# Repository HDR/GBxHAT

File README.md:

# GBxHAT

**A GBxCart RW in PiZero Hat format**

Purchase on [OSHPark](https://oshpark.com/shared_projects/nTx9yzmZ)

Uses the original schematic by [InsideGadgets](https://github.com/insidegadgets/GBxCart-RW) with some changes

Uses the Pi Zero HAT template by [Mike Lawrence](https://github.com/mikelawrence/RPi_Zero_pHat_Template)

The CH340 was removed, as TX and RX are connected straight to the pi zero

[Interactive BOM](https://martinrefseth.com/ibom/GBxHat)

**Keep in mind that this is untested and has no software**

## Images

## Notes

- Please cut pin 4 on the pi if your hat is not the revision published after July 18th 2020.

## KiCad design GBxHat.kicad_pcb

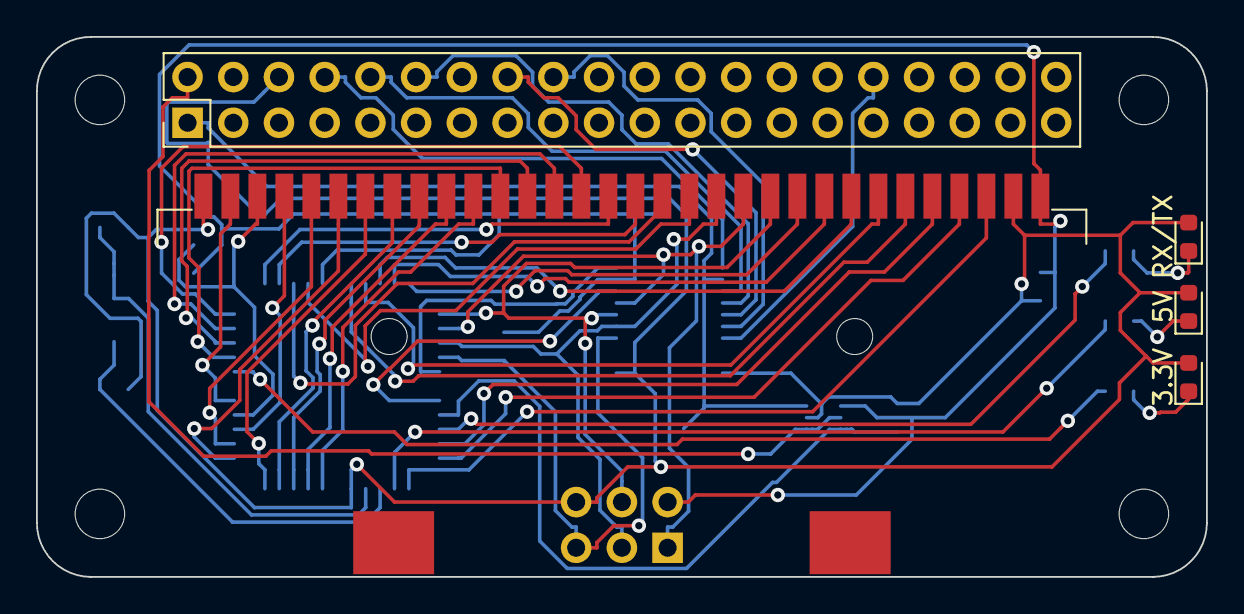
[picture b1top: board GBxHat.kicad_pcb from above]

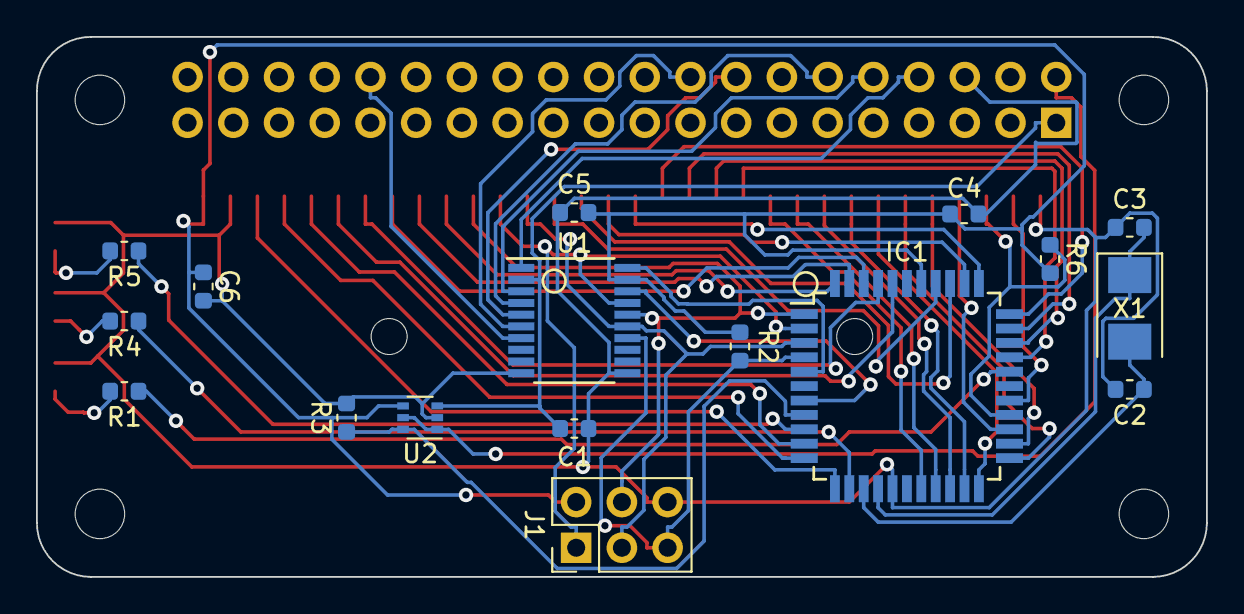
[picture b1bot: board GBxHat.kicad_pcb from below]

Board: 2 copper layers, 65.0 x 30.0 mm, 26 parts (17 on the bottom side), 51 nets.

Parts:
3.3V: 3.3V LED; LED_0603_1608Metric
5V: 5V LED; LED_0603_1608Metric
C1, C4, C5, C6: 0.1uF; C_0603_1608Metric
C2, C3: 18pF; C_0603_1608Metric
IC1: ATMEGA8515L-8AU; TQFP-44_10x10mm_P0.8mm
J0: Pi Zero; PinHeader_2x20_P2.54mm_Vertical
J1: AVR_SPI_6; PinHeader_2x03_P2.54mm_Vertical
MH1, MH2, MH3, MH4: MountingHole; RPi_Hat_Mounting_Hole
R1, R2, R3, R4, R5, R6: 10K; R_0603_1608Metric
RX/TX: RX/TX LED; LED_0603_1608Metric
U1: TXB0108PWR; TSSOP-20_4.4x6.5mm_P0.65mm
U2: NLAS4157; SOT-363_SC-70-6
U$1: GB_CARTWITH_HOLES; DSL_Cartridge_Reader
X1: 8MHz; Crystal_SMD_5032-2Pin_5.0x3.2mm

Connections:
3.3V: C1.1, J0.1, U1.2, U2.3
5V: J0.2, U2.1, U2.5
/*MREQ/CS: IC1.10, U$1.5
/*RD: IC1.11, U$1.4
/*RESET/CS2: IC1.26, R6.1, U$1.30
/*WR: IC1.12, U$1.3
/A0: IC1.40, U$1.6
/A1: IC1.41, U$1.7
/A2: IC1.42, U$1.8
/A3: IC1.43, U$1.9
/A4: IC1.44, U$1.10
/A5/MOSI: IC1.1, J1.4, U1.16, U$1.11
/A6/MISO: IC1.2, J1.1, U1.17, U$1.12
/A7/SCK: IC1.3, J1.3, U1.15, U$1.13
/A8: IC1.37, U$1.14
/A9: IC1.36, U$1.15
/A10: IC1.35, U$1.16
/A11: IC1.34, U$1.17
/A12: IC1.33, U$1.18
/A13: IC1.32, U$1.19
/A14: IC1.31, U$1.20
/A15: IC1.30, U$1.21
/ATMEGA_RX_OUT: IC1.5, U1.20
/ATMEGA_TX_OUT: IC1.7, U1.18
/AUDIO_IN: IC1.27, U$1.31
/D0: IC1.18, U$1.22
/D1: IC1.19, U$1.23
/D2: IC1.20, U$1.24
/D3: IC1.21, U$1.25
/D4: IC1.22, U$1.26
/D5: IC1.23, U$1.27
/D6: IC1.24, U$1.28
/D7: IC1.25, U$1.29
/PI_MISO: J0.12, U1.4
/PI_MOSI: J0.16, U1.5
/PI_RESET: J0.32, U1.7
/PI_RX_IN: J0.8, U1.1
/PI_SCK: J0.18, U1.6
/PI_TX_IN: J0.10, U1.3
/RESET: IC1.4, J1.5, R2.1, U1.14
/SPDT_SEL: IC1.8, R3.1, U2.6
GND: 3.3V.2, 5V.2, C1.2, C2.2, C3.2, C4.2, C5.2, C6.2, IC1.16, J0.6, J1.6, R3.2, RX/TX.2, U1.10, U1.11, U2.2, U$1.2, U$1.32
unnamed: C2.1, IC1.14, X1.2
unnamed: C3.1, IC1.15, X1.1
unnamed: IC1.9, R5.1
unnamed: IC1.13, R4.1
unnamed: IC1.29, R1.1
unnamed: 3.3V.1, R1.2
unnamed: 5V.1, R4.2
unnamed: R5.2, RX/TX.1
VCC: C4.1, C5.1, C6.1, IC1.38, J1.2, R2.2, R6.2, U1.19, U2.4, U$1.1

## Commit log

2020-07-16 add files
2020-07-16 Create LICENSE
2020-07-16 add images to readme
2020-07-16 Relocated & Updated LED's
    Changed the identifiers for the LED's to match the GBxCart RW
    Centered LED's on board
2020-07-17 Fixed logic level issues & removed voltage regulator
    - Fixed the issue where 5v logic was connected to the Pi zero which is not 5v tolerant
    - Removed the NLAS4157, the 3.3v on the Pi zero itself is now being used instead
    - Removed the 74LVC1G126 chips since RX and TX are now connected to the TXB0108
2020-07-17 Update images and add Gerbers
2020-07-18 Fix an issue where VCC was bound to pin4 on the pi
2020-07-20 update images
2020-08-06 Moved the LED resistors to the other side of the board as they were in the way of the cart slot
2020-08-06 small update
2020-08-08 Fix grounding issue and schematic issue
